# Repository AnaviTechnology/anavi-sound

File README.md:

# ANAVI Sound pHAT

ANAVI Sound pHAT is an open source hardware Raspberry Pi pHAT (add-on board). It features:

* Slot for PIR motion sensor
* Slots for up to 3 plug and play I2C sensors for temperature, barometric pressure, humidity and light
* UART (Universal asynchronous receiver/transmitter) pins for debugging
* EEPROM

# License

The project is released under the [Creative Commons Attribution-ShareAlike 4.0 International (CC BY-SA 4.0)](https://creativecommons.org/licenses/by-sa/4.0/).

Note: This is a human-readable summary of (and not a substitute for) the [license](https://creativecommons.org/licenses/by-sa/4.0/legalcode).

You are free to:

Share — copy and redistribute the material in any medium or format Adapt — remix, transform, and build upon the material for any purpose, even commercially. The licensor cannot revoke these freedoms as long as you follow the license terms. Under the following terms:

Attribution — You must give appropriate credit, provide a link to the license, and indicate if changes were made. You may do so in any reasonable manner, but not in any way that suggests the licensor endorses you or your use. ShareAlike — If you remix, transform, or build upon the material, you must distribute your contributions under the same license as the original. No additional restrictions — You may not apply legal terms or technological measures that legally restrict others from doing anything the license permits. Notices:

You do not have to comply with the license for elements of the material in the public domain or where your use is permitted by an applicable exception or limitation. No warranties are given. The license may not give you all of the permissions necessary for your intended use. For example, other rights such as publicity, privacy, or moral rights may limit how you use the material.

You will have to provide a link to the original creator of the project http://www.anavi.technology on any documentation or website.

Credit can be attributed through a link to the creator website: http://www.anavi.technology

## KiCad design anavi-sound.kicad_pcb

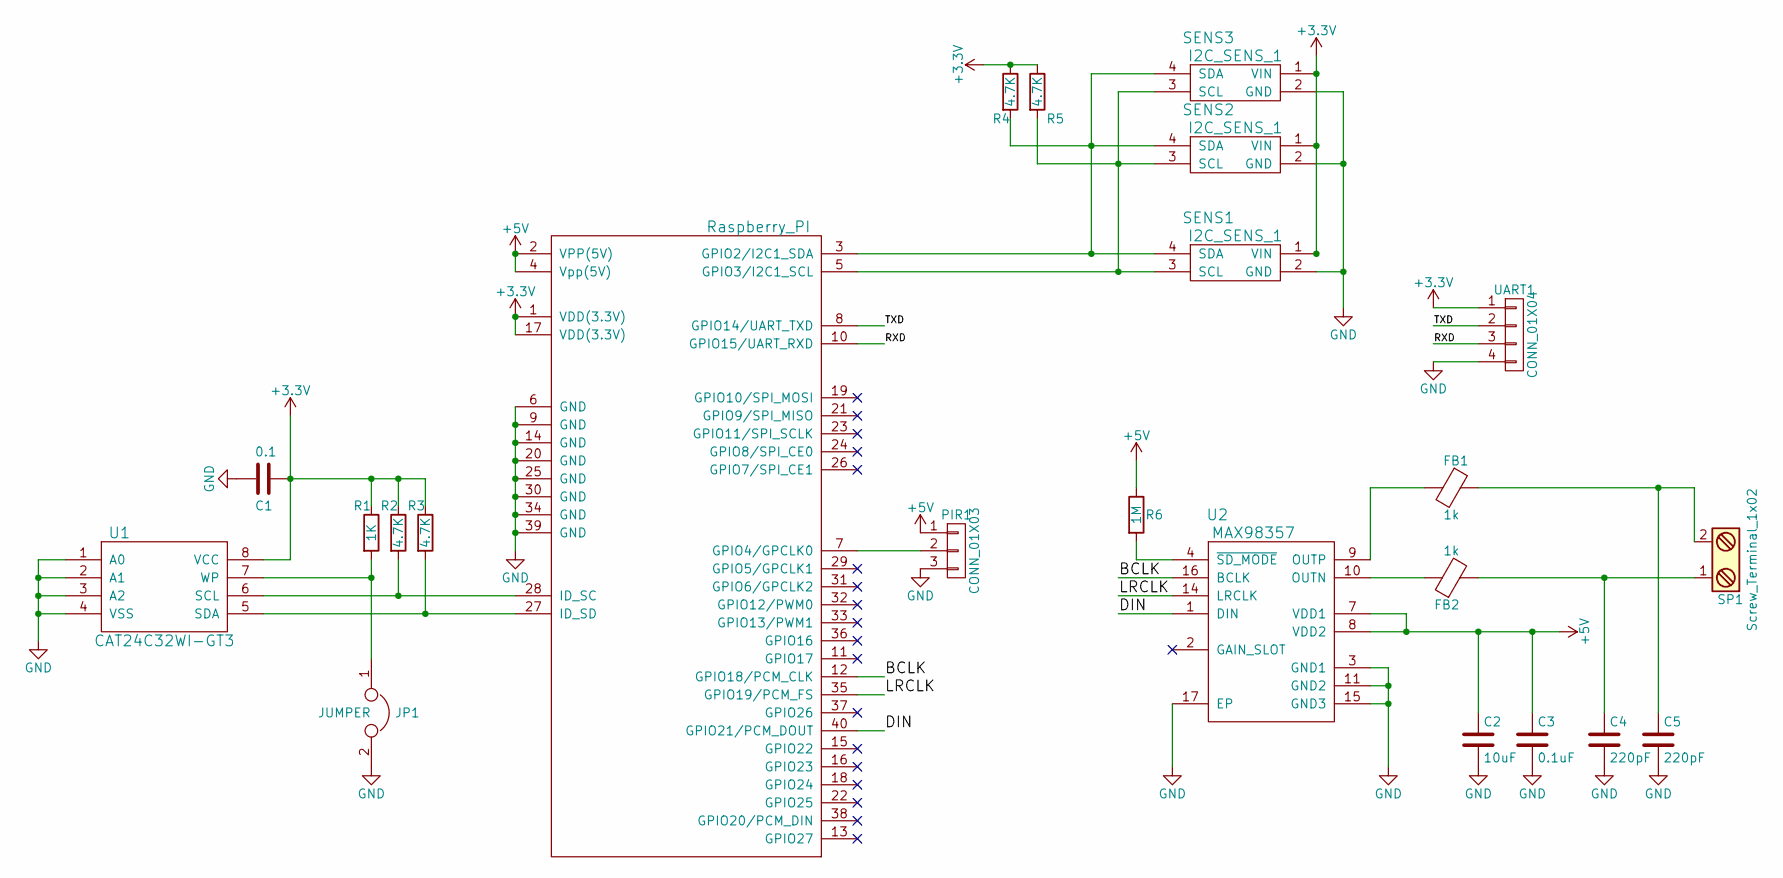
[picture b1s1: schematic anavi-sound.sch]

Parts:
C1: 0.1; C_0603
C2: 10uF; C_0603
C3: 0.1uF; C_0603
C4, C5: 220pF; C_0603
FB1, FB2: 1k; R_0603
JP1: JUMPER; Pin_Header_Straight_1x02
PIR1: CONN_01X03; Pin_Header_Straight_1x03
R1: 1K; R_0603
R2, R3, R4, R5: 4.7K; R_0603
R6: 1M; R_0603
RASP_CONN1: Raspberry_PI; Pin_Header_Straight_2x20
SENS1, SENS2, SENS3: I2C_SENS_1; Pin_Header_Straight_1x04
SP1: Screw_Terminal_1x02; TerminalBlock_Pheonix_MKDS1.5-2pol
U1: CAT24C32WI-GT3; DIP-8_W7.62mm
U2: MAX98357; QFN-16-1EP_3x3mm_Pitch0.5mm
UART1: CONN_01X04; Pin_Header_Straight_1x04

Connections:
+3V3: C1.1, R1.1, R2.1, R3.1, R4.1, R5.1, RASP_CONN1.1 (VDD(3.3V)), RASP_CONN1.17 (VDD(3.3V)), SENS1.1 (VIN), SENS2.1 (VIN), SENS3.1 (VIN), U1.8 (VCC), UART1.1; also elsewhere on the board
+5V: C2.1, C3.1, PIR1.1, R6.1, RASP_CONN1.2 (VPP(5V)), RASP_CONN1.4 (Vpp(5V)), U2.7 (VDD1), U2.8 (VDD2); also elsewhere on the board
/BCLK: RASP_CONN1.12 (GPIO18/PCM_CLK), U2.16 (BCLK)
/DIN: RASP_CONN1.40 (GPIO21/PCM_DOUT), U2.1 (DIN)
/LRCLK: RASP_CONN1.35 (GPIO19/PCM_FS), U2.14 (LRCLK)
/RXD: RASP_CONN1.10 (GPIO15/UART_RXD), UART1.3; also elsewhere on the board
/TXD: RASP_CONN1.8 (GPIO14/UART_TXD), UART1.2; also elsewhere on the board
GND: C1.2, C2.2, C3.2, C4.2, C5.2, JP1.2, PIR1.3, RASP_CONN1.6 (GND), RASP_CONN1.9 (GND), RASP_CONN1.14 (GND), RASP_CONN1.20 (GND), RASP_CONN1.25 (GND), RASP_CONN1.30 (GND), RASP_CONN1.34 (GND), RASP_CONN1.39 (GND), SENS1.2 (GND), SENS2.2 (GND), SENS3.2 (GND), U1.1 (A0), U1.2 (A1), U1.3 (A2), U1.4 (VSS), U2.3 (GND1), U2.11 (GND2), U2.15 (GND3), U2.17 (EP), UART1.4; also elsewhere on the board
unnamed: C4.1, FB2.2, SP1.1
unnamed: C5.1, FB1.1, SP1.2
unnamed: FB1.2, U2.9 (OUTP)
unnamed: FB2.1, U2.10 (OUTN)
unnamed: JP1.1, R1.2, U1.7 (WP)
unnamed 13: PIR1.2, RASP_CONN1.7 (GPIO4/GPCLK0); also elsewhere on the board
unnamed: R2.2, RASP_CONN1.28 (ID_SC), U1.6 (SCL)
unnamed: R3.2, RASP_CONN1.27 (ID_SD), U1.5 (SDA)
unnamed: R4.2, RASP_CONN1.3 (GPIO2/I2C1_SDA), SENS1.4 (SDA), SENS2.4 (SDA), SENS3.4 (SDA)
unnamed: R5.2, RASP_CONN1.5 (GPIO3/I2C1_SCL), SENS1.3 (SCL), SENS2.3 (SCL), SENS3.3 (SCL)
unnamed: R6.2, U2.4 (~SD_MODE)

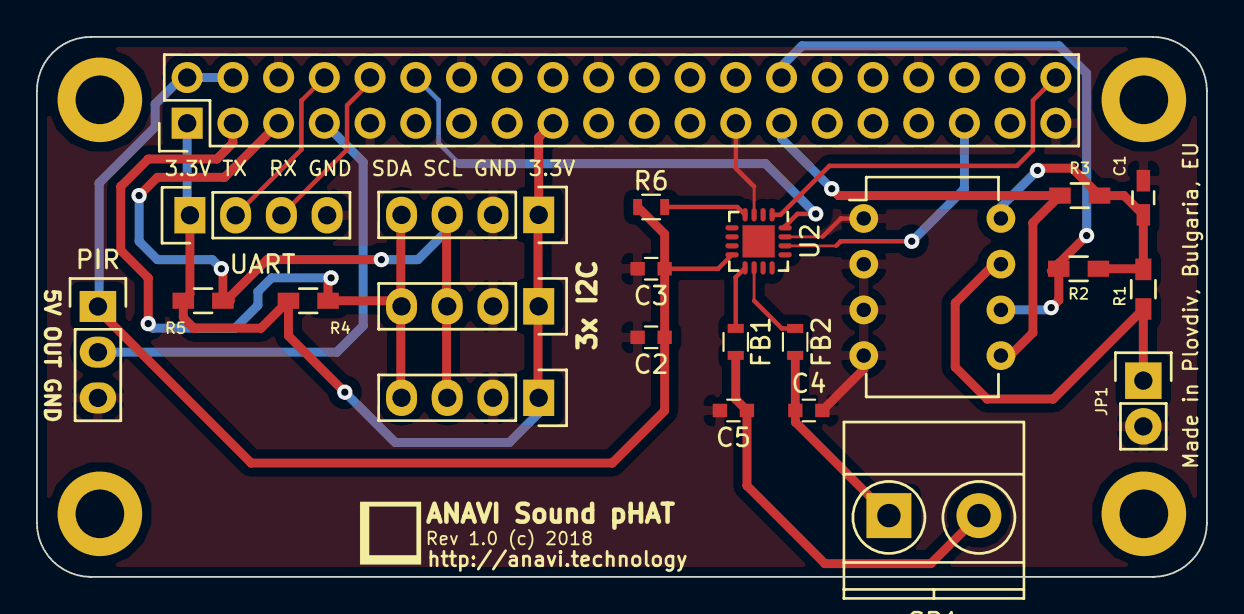
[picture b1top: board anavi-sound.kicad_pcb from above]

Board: 2 copper layers, 65.0 x 30.0 mm, 27 parts (0 on the bottom side), 19 nets.

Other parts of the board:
PIR: CONN_01X03; Pin_Header_Straight_1x03
REF1, REF2, REF3, REF4: MountingHole_2.7mm_M2.5_DIN965_Pad
UART: CONN_01X04; Pin_Header_Straight_1x04

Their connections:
+3V3: UART.1; also elsewhere on the board
+5V: PIR.1; also elsewhere on the board
/RXD: UART.3; also elsewhere on the board
/TXD: UART.2; also elsewhere on the board
GND: PIR.3, UART.4; also elsewhere on the board
unnamed 13: PIR.2; also elsewhere on the board

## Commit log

2018-05-10 anavi-sound.sch: Fix annotations
2018-05-10 anavi-sound.kicad_pcb: Cleanup
2018-05-10 anavi-sound.sch: Add terminal for the speaker
2018-05-11 MAX98357A routing
    Update footprint and routing.

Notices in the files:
anavi-sound.kicad_pcb:
Rev 1.0 (c) 2018
